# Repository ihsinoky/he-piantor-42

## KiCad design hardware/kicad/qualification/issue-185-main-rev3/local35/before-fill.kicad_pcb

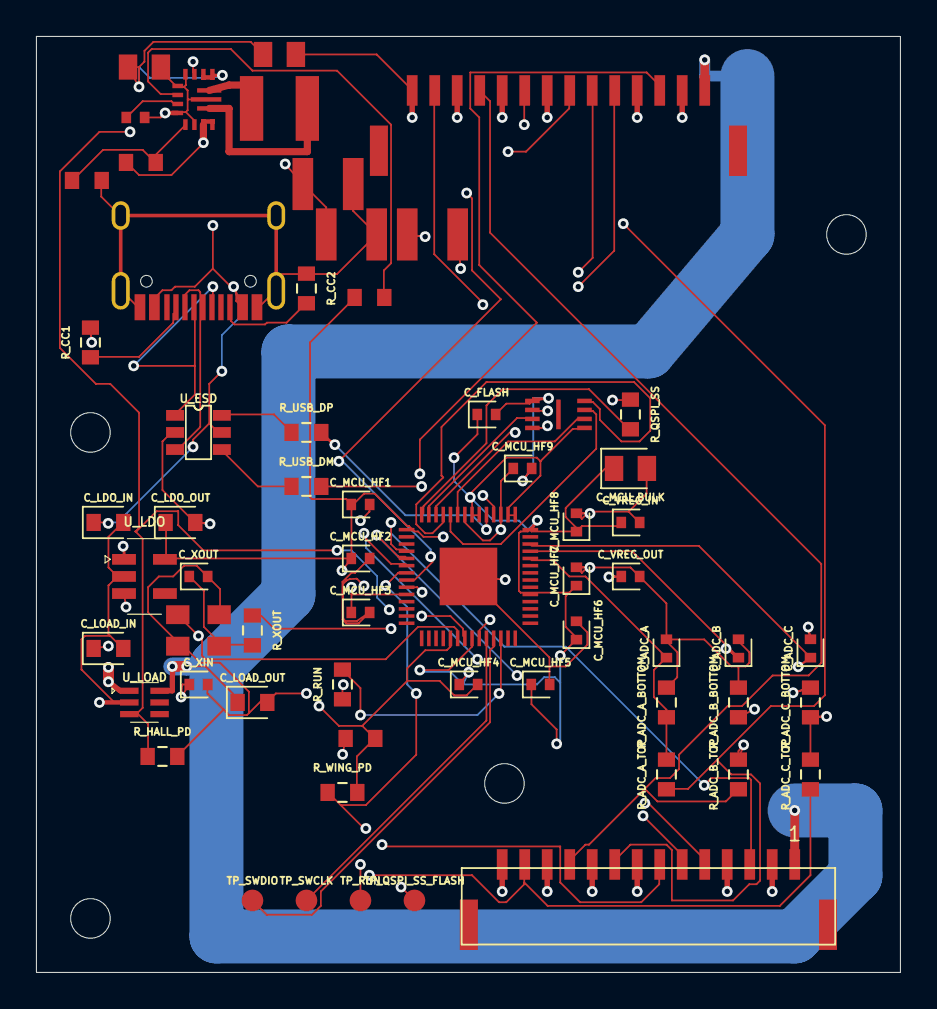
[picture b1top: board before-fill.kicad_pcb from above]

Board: 4 copper layers, 48.0 x 52.0 mm, 66 parts (0 on the bottom side), 44 nets.

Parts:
C1: 15pF; C1
C2: 15pF; C2
C3: 100nF; C3
C4: 100nF; C4
C5: 100nF; C5
C6: 100nF; C6
C7: 100nF; C7
C8: 100nF; C8
C9: 100nF; C9
C10: 100nF; C10
C11: 100nF; C11
C12: 1uF; C12
C13: 1uF; C13
C14: 10uF; C14
C15: 100nF; C15
C16: 1uF; C16
C17: 1uF; C17
C18: 1uF; C18
C19: 1uF; C19
C20: 1nF; C20
C21: 1nF; C21
C22: 1nF; C22
C23: 22uF 16V X6S 0805; C23
C24: 22uF 16V X6S 0805; C24
C25: 100nF; C25
C26: 22uF 16V X7R 1210; C26
C27: 22uF 16V X7R 1210; C27
C28: 22uF 16V X7R 1210; C28
H1: NPTH_2.2mm; H1
H2: NPTH_2.2mm; H2
H3: NPTH_2.2mm; H3
H4: NPTH_2.2mm; H4
J1: TYPE-C-31-M-12; J1
J2: BM14B-GHS-TBT(LF)(SN); J2
J3: BM14B-GHS-TBT(LF)(SN); J3
L1: 1.5uH XFL4020-152MEC; L1
R1: 5.1k; R1
R2: 5.1k; R2
R3: 27; R3
R4: 27; R4
R5: 1k; R5
R6: 100k; R6
R7: 100k; R7
R8: 10k; R8
R9: 1k; R9
R10: 6.8k; R10
R11: 10k; R11
R12: 6.8k; R12
R13: 10k; R13
R14: 6.8k; R14
R15: 10k; R15
R16: 100k; R16
R17: 54.9k 0.1% 25ppm/K; R17
R18: 10k 0.1% 25ppm/K; R18
R19: 100k; R19
TP1: TestPoint; TP1
TP2: TestPoint; TP2
TP3: TestPoint; TP3
TP4: TestPoint; TP4
U1: RP2040; U1
U2: USBLC6-2SC6; U2
U3: W25Q16JVUXIQ; U3
U4: AP2112K-3.3TRG1; U4
U5: TPS22919DCKR; U5
U6: TPS63070RNMR; U6
Y1: ABM8-272-T3; Y1

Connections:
ADC_A: C20.1, R10.2, R11.1, U1.38
ADC_B: C21.1, R12.2, R13.1, U1.39
ADC_C: C22.1, R14.2, R15.1, U1.40
CC1: J1.3, R1.1
CC2: J1.10, R2.1
FB_5V2: R17.2, R18.1, U6.5
GND: C1.2, C2.2, C3.2, C4.2, C5.2, C6.2, C7.2, C8.2, C9.2, C10.2, C11.2, C12.2, C13.2, C14.2, C15.2, C16.2, C17.2, C18.2, C19.2, C20.2, C21.2, C22.2, C23.2, C24.2, C25.2, C26.2, C27.2, C28.2, J1.1, J1.12, J1.13, J2.2, J2.4, J2.8, J2.10, J2.12, J2.14, J3.2, J3.4, J3.8, J3.10, J3.12, J3.14, R1.2, R2.2, R6.2, R7.2, R11.2, R13.2, R15.2, R16.2, R18.2, U1.19, U1.57, U2.2, U3.4, U4.2, U5.2, U6.1, U6.4, U6.6, U6.10, U6.15, Y1.2, Y1.4
HALL_5V: C19.1, J2.1, J3.1, U5.6
HALL_PWR_EN: R7.1, U1.9, U5.3, U6.14
MUX_A0: J2.3, J3.3, U1.4
MUX_A1: J2.5, J3.5, U1.5
MUX_A2: J2.6, J3.6, U1.6
MUX_EN1: J3.7, R16.1, U1.8
MUX_OUT_A: J2.9, J3.9, R10.1
MUX_OUT_B: J2.11, J3.11, R12.1
MUX_OUT_C: J2.13, J3.13, R14.1
QSPI_SCLK: U1.52, U3.6
QSPI_SD0: U1.53, U3.5
QSPI_SD1: U1.55, U3.2
QSPI_SD2: U1.54, U3.3
QSPI_SD3: U1.51, U3.7
QSPI_SS_FLASH: R5.2, TP4.1, U3.1
QSPI_SS_MCU: R5.1, U1.56
RAIL_PG: R19.2, U6.2
RUN: R8.2, TP3.1, U1.26
SW1: L1.1, U6.11
SW2: L1.2, U6.9
SWCLK: TP2.1, U1.24
SWDIO: TP1.1, U1.25
USB_DM: R4.2, U1.46
USB_DM_CONN: J1.5, J1.8, U2.3
USB_DM_ESD: R4.1, U2.4
USB_DP: R3.2, U1.47
USB_DP_CONN: J1.4, J1.9, U2.1
USB_DP_ESD: R3.1, U2.6
V1V1: C11.1, C13.1, U1.23, U1.45, U1.50
V3V3: C3.1, C4.1, C5.1, C6.1, C7.1, C8.1, C9.1, C10.1, C12.1, C14.1, C15.1, C17.1, R8.1, R19.1, U1.1, U1.10, U1.22, U1.33, U1.42, U1.43, U1.44, U1.48, U1.49, U3.8, U4.5
V5V2: C26.1, C27.1, C28.1, R17.1, U5.1, U6.7, U6.8
VAUX: C25.1, U6.3
VBUS: C16.1, C18.1, C23.1, C24.1, J1.2, J1.11, U2.5, U4.1, U4.3, U6.12, U6.13
WING_EN: J2.7, R6.1, U1.7
XIN: C1.1, U1.20, Y1.1
XOUT: R9.2, U1.21
XOUT_XTAL: C2.1, R9.1, Y1.3

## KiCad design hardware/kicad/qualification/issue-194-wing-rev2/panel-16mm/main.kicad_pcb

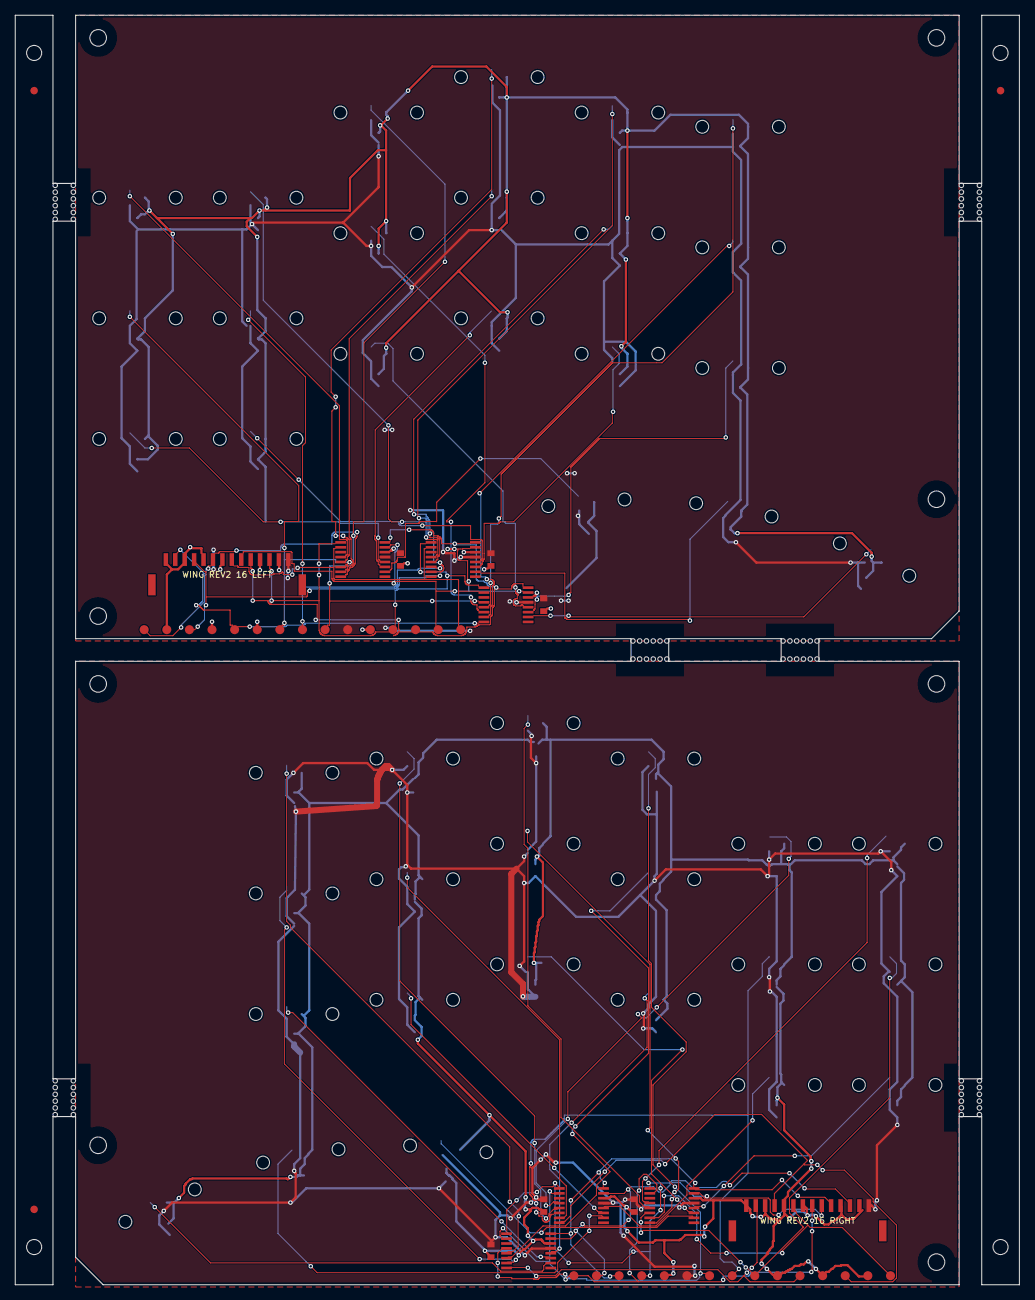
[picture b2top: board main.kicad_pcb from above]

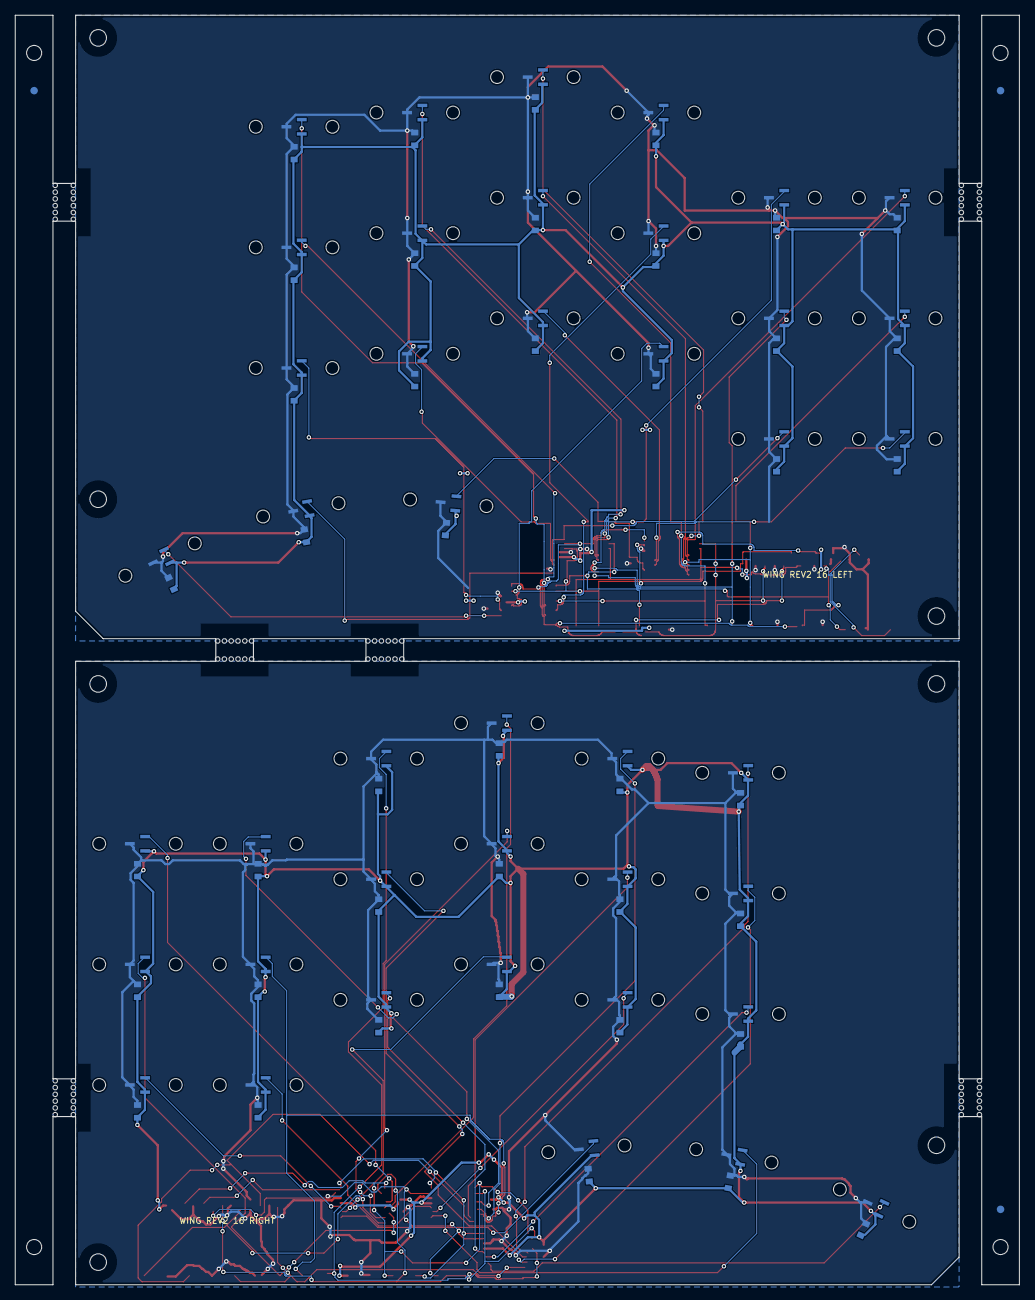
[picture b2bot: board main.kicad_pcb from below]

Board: 2 copper layers, 133.2 x 168.4 mm, 299 parts (84 on the bottom side), 60 nets.

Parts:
FID1, FID2, FID3: Fiducial_1mm
L_C_HA0, L_C_HA1, L_C_HA2, L_C_HA3, L_C_HA4, L_C_HA5, L_C_HA6: GRM188R71C104KA01D; capacitor
L_C_HB0, L_C_HB1, L_C_HB2, L_C_HB3, L_C_HB4, L_C_HB5, L_C_HB6: GRM188R71C104KA01D; capacitor
L_C_HC0, L_C_HC1, L_C_HC2, L_C_HC3, L_C_HC4, L_C_HC5, L_C_HC6: GRM188R71C104KA01D; capacitor
L_C_MUX_A: GRM188R71C104KA01D; capacitor
L_C_MUX_B: GRM188R71C104KA01D; capacitor
L_C_MUX_C: GRM188R71C104KA01D; capacitor
L_H1, L_H2, L_H3, L_H4: NPTH_2.2; NPTH
L_J_WING: BM14B-GHS-TBT(LF)(SN); connector
L_MH_1_1, L_MH_1_2, L_MH_2_1, L_MH_2_2, L_MH_3_1, L_MH_3_2, L_MH_4_1, L_MH_4_2, L_MH_5_1, L_MH_5_2, L_MH_6_1, L_MH_6_2, L_MH_7_1, L_MH_7_2, L_MH_8_1, L_MH_8_2, L_MH_9_1, L_MH_9_2, L_MH_10_1, L_MH_10_2, L_MH_11_1, L_MH_11_2, L_MH_12_1, L_MH_12_2, L_MH_13_1, L_MH_13_2, L_MH_14_1, L_MH_14_2, L_MH_15_1, L_MH_15_2, L_MH_16_1, L_MH_16_2, L_MH_17_1, L_MH_17_2, L_MH_18_1, L_MH_18_2, L_MH_19_1, L_MH_19_2, L_MH_20_1, L_MH_20_2, L_MH_21_1, L_MH_21_2: NPTH_1.7; NPTH
L_TP_H_CTR_RAW: PCB_PAD_1.2MM; testpoint
L_TP_H_DIAG_RAW: PCB_PAD_1.2MM; testpoint
L_TP_H_N_RAW: PCB_PAD_1.2MM; testpoint
L_TP_W_A0, L_TP_W_A1, L_TP_W_A2: PCB_PAD_1.2MM; testpoint
L_TP_W_EN: PCB_PAD_1.2MM; testpoint
L_TP_W_GND: PCB_PAD_1.2MM; testpoint
L_TP_W_GND_A: PCB_PAD_1.2MM; testpoint
L_TP_W_GND_B: PCB_PAD_1.2MM; testpoint
L_TP_W_GND_C: PCB_PAD_1.2MM; testpoint
L_TP_W_H5V: PCB_PAD_1.2MM; testpoint
L_TP_W_MUXA: PCB_PAD_1.2MM; testpoint
L_TP_W_MUXB: PCB_PAD_1.2MM; testpoint
L_TP_W_MUXC: PCB_PAD_1.2MM; testpoint
L_U_HA0, L_U_HA1, L_U_HA2, L_U_HA3, L_U_HA4, L_U_HA5, L_U_HA6: DRV5055A3QDBZR; hall
L_U_HB0, L_U_HB1, L_U_HB2, L_U_HB3, L_U_HB4, L_U_HB5, L_U_HB6: DRV5055A3QDBZR; hall
L_U_HC0, L_U_HC1, L_U_HC2, L_U_HC3, L_U_HC4, L_U_HC5, L_U_HC6: DRV5055A3QDBZR; hall
L_U_MUX_A: TMUX1208PWR; mux
L_U_MUX_B: TMUX1208PWR; mux
L_U_MUX_C: TMUX1208PWR; mux
MB_1, MB_2, MB_3, MB_4, MB_5, MB_6, MB_7, MB_8, MB_9, MB_10, MB_11, MB_12, MB_13, MB_14, MB_15, MB_16, MB_17, MB_18, MB_19, MB_20, MB_21, MB_22, MB_23, MB_24, MB_25, MB_26, MB_27, MB_28, MB_29, MB_30, MB_31, MB_32, MB_33, MB_34, MB_35, MB_36, MB_37, MB_38, MB_39, MB_40, MB_41, MB_42, MB_43, MB_44, MB_45, MB_46, MB_47, MB_48, MB_49, MB_50, MB_51, MB_52, MB_53, MB_54, MB_55, MB_56, MB_57, MB_58, MB_59, MB_60, MB_61, MB_62, MB_63, MB_64, MB_65, MB_66, MB_67, MB_68, MB_69, MB_70, MB_71, MB_72: NPTH_0.6
R_C_HA0, R_C_HA1, R_C_HA2, R_C_HA3, R_C_HA4, R_C_HA5, R_C_HA6: GRM188R71C104KA01D; capacitor
R_C_HB0, R_C_HB1, R_C_HB2, R_C_HB3, R_C_HB4, R_C_HB5, R_C_HB6: GRM188R71C104KA01D; capacitor
R_C_HC0, R_C_HC1, R_C_HC2, R_C_HC3, R_C_HC4, R_C_HC5, R_C_HC6: GRM188R71C104KA01D; capacitor
R_C_MUX_A: GRM188R71C104KA01D; capacitor
R_C_MUX_B: GRM188R71C104KA01D; capacitor
R_C_MUX_C: GRM188R71C104KA01D; capacitor
R_H1, R_H2, R_H3, R_H4: NPTH_2.2; NPTH
R_J_WING: BM14B-GHS-TBT(LF)(SN); connector
R_MH_1_1, R_MH_1_2, R_MH_2_1, R_MH_2_2, R_MH_3_1, R_MH_3_2, R_MH_4_1, R_MH_4_2, R_MH_5_1, R_MH_5_2, R_MH_6_1, R_MH_6_2, R_MH_7_1, R_MH_7_2, R_MH_8_1, R_MH_8_2, R_MH_9_1, R_MH_9_2, R_MH_10_1, R_MH_10_2, R_MH_11_1, R_MH_11_2, R_MH_12_1, R_MH_12_2, R_MH_13_1, R_MH_13_2, R_MH_14_1, R_MH_14_2, R_MH_15_1, R_MH_15_2, R_MH_16_1, R_MH_16_2, R_MH_17_1, R_MH_17_2, R_MH_18_1, R_MH_18_2, R_MH_19_1, R_MH_19_2, R_MH_20_1, R_MH_20_2, R_MH_21_1, R_MH_21_2: NPTH_1.7; NPTH
R_TP_H_CTR_RAW: PCB_PAD_1.2MM; testpoint
R_TP_H_DIAG_RAW: PCB_PAD_1.2MM; testpoint
R_TP_H_N_RAW: PCB_PAD_1.2MM; testpoint
R_TP_W_A0, R_TP_W_A1, R_TP_W_A2: PCB_PAD_1.2MM; testpoint
R_TP_W_EN: PCB_PAD_1.2MM; testpoint
R_TP_W_GND: PCB_PAD_1.2MM; testpoint
R_TP_W_GND_A: PCB_PAD_1.2MM; testpoint
R_TP_W_GND_B: PCB_PAD_1.2MM; testpoint
R_TP_W_GND_C: PCB_PAD_1.2MM; testpoint
R_TP_W_H5V: PCB_PAD_1.2MM; testpoint
R_TP_W_MUXA: PCB_PAD_1.2MM; testpoint
R_TP_W_MUXB: PCB_PAD_1.2MM; testpoint
R_TP_W_MUXC: PCB_PAD_1.2MM; testpoint
R_U_HA0, R_U_HA1, R_U_HA2, R_U_HA3, R_U_HA4, R_U_HA5, R_U_HA6: DRV5055A3QDBZR; hall
R_U_HB0, R_U_HB1, R_U_HB2, R_U_HB3, R_U_HB4, R_U_HB5, R_U_HB6: DRV5055A3QDBZR; hall
R_U_HC0, R_U_HC1, R_U_HC2, R_U_HC3, R_U_HC4, R_U_HC5, R_U_HC6: DRV5055A3QDBZR; hall
R_U_MUX_A: TMUX1208PWR; mux
R_U_MUX_B: TMUX1208PWR; mux
R_U_MUX_C: TMUX1208PWR; mux
TOOL_1, TOOL_2, TOOL_3, TOOL_4: NPTH_2

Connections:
L_GND: L_C_HA0.2, L_C_HA1.2, L_C_HA2.2, L_C_HA3.2, L_C_HA4.2, L_C_HA5.2, L_C_HA6.2, L_C_HB0.2, L_C_HB1.2, L_C_HB2.2, L_C_HB3.2, L_C_HB4.2, L_C_HB5.2, L_C_HB6.2, L_C_HC0.2, L_C_HC1.2, L_C_HC2.2, L_C_HC3.2, L_C_HC4.2, L_C_HC5.2, L_C_HC6.2, L_C_MUX_A.2, L_C_MUX_B.2, L_C_MUX_C.2, L_J_WING.2, L_J_WING.4, L_J_WING.8, L_J_WING.10, L_J_WING.12, L_J_WING.14, L_TP_W_GND.1, L_TP_W_GND_A.1, L_TP_W_GND_B.1, L_TP_W_GND_C.1, L_U_HA0.3, L_U_HA1.3, L_U_HA2.3, L_U_HA3.3, L_U_HA4.3, L_U_HA5.3, L_U_HA6.3, L_U_HB0.3, L_U_HB1.3, L_U_HB2.3, L_U_HB3.3, L_U_HB4.3, L_U_HB5.3, L_U_HB6.3, L_U_HC0.3, L_U_HC1.3, L_U_HC2.3, L_U_HC3.3, L_U_HC4.3, L_U_HC5.3, L_U_HC6.3, L_U_MUX_A.14, L_U_MUX_B.14, L_U_MUX_C.14
L_HALL_5V: L_C_HA0.1, L_C_HA1.1, L_C_HA2.1, L_C_HA3.1, L_C_HA4.1, L_C_HA5.1, L_C_HA6.1, L_C_HB0.1, L_C_HB1.1, L_C_HB2.1, L_C_HB3.1, L_C_HB4.1, L_C_HB5.1, L_C_HB6.1, L_C_HC0.1, L_C_HC1.1, L_C_HC2.1, L_C_HC3.1, L_C_HC4.1, L_C_HC5.1, L_C_HC6.1, L_C_MUX_A.1, L_C_MUX_B.1, L_C_MUX_C.1, L_J_WING.1, L_TP_W_H5V.1, L_U_HA0.1, L_U_HA1.1, L_U_HA2.1, L_U_HA3.1, L_U_HA4.1, L_U_HA5.1, L_U_HA6.1, L_U_HB0.1, L_U_HB1.1, L_U_HB2.1, L_U_HB3.1, L_U_HB4.1, L_U_HB5.1, L_U_HB6.1, L_U_HC0.1, L_U_HC1.1, L_U_HC2.1, L_U_HC3.1, L_U_HC4.1, L_U_HC5.1, L_U_HC6.1, L_U_MUX_A.13, L_U_MUX_B.13, L_U_MUX_C.13
L_H_A0_RAW: L_U_HA0.2, L_U_MUX_A.4
L_H_A1_RAW: L_U_HA1.2, L_U_MUX_A.5
L_H_A2_RAW: L_TP_H_CTR_RAW.1, L_U_HA2.2, L_U_MUX_A.6
L_H_A3_RAW: L_U_HA3.2, L_U_MUX_A.7
L_H_A4_RAW: L_U_HA4.2, L_U_MUX_A.12
L_H_A5_RAW: L_U_HA5.2, L_U_MUX_A.11
L_H_A6_RAW: L_U_HA6.2, L_U_MUX_A.10
L_H_B0_RAW: L_U_HB0.2, L_U_MUX_B.4
L_H_B1_RAW: L_U_HB1.2, L_U_MUX_B.5
L_H_B2_RAW: L_TP_H_N_RAW.1, L_U_HB2.2, L_U_MUX_B.6
L_H_B3_RAW: L_U_HB3.2, L_U_MUX_B.7
L_H_B4_RAW: L_U_HB4.2, L_U_MUX_B.12
L_H_B5_RAW: L_U_HB5.2, L_U_MUX_B.11
L_H_B6_RAW: L_U_HB6.2, L_U_MUX_B.10
L_H_C0_RAW: L_TP_H_DIAG_RAW.1, L_U_HC0.2, L_U_MUX_C.4
L_H_C1_RAW: L_U_HC1.2, L_U_MUX_C.5
L_H_C2_RAW: L_U_HC2.2, L_U_MUX_C.6
L_H_C3_RAW: L_U_HC3.2, L_U_MUX_C.7
L_H_C4_RAW: L_U_HC4.2, L_U_MUX_C.12
L_H_C5_RAW: L_U_HC5.2, L_U_MUX_C.11
L_H_C6_RAW: L_U_HC6.2, L_U_MUX_C.10
L_MUX_A0: L_J_WING.3, L_TP_W_A0.1, L_U_MUX_A.1, L_U_MUX_B.1, L_U_MUX_C.1
L_MUX_A1: L_J_WING.5, L_TP_W_A1.1, L_U_MUX_A.16, L_U_MUX_B.16, L_U_MUX_C.16
L_MUX_A2: L_J_WING.6, L_TP_W_A2.1, L_U_MUX_A.15, L_U_MUX_B.15, L_U_MUX_C.15
L_MUX_OUT_A: L_J_WING.9, L_TP_W_MUXA.1, L_U_MUX_A.8
L_MUX_OUT_B: L_J_WING.11, L_TP_W_MUXB.1, L_U_MUX_B.8
L_MUX_OUT_C: L_J_WING.13, L_TP_W_MUXC.1, L_U_MUX_C.8
L_WING_EN: L_J_WING.7, L_TP_W_EN.1, L_U_MUX_A.2, L_U_MUX_B.2, L_U_MUX_C.2
R_GND: R_C_HA0.2, R_C_HA1.2, R_C_HA2.2, R_C_HA3.2, R_C_HA4.2, R_C_HA5.2, R_C_HA6.2, R_C_HB0.2, R_C_HB1.2, R_C_HB2.2, R_C_HB3.2, R_C_HB4.2, R_C_HB5.2, R_C_HB6.2, R_C_HC0.2, R_C_HC1.2, R_C_HC2.2, R_C_HC3.2, R_C_HC4.2, R_C_HC5.2, R_C_HC6.2, R_C_MUX_A.2, R_C_MUX_B.2, R_C_MUX_C.2, R_J_WING.2, R_J_WING.4, R_J_WING.8, R_J_WING.10, R_J_WING.12, R_J_WING.14, R_TP_W_GND.1, R_TP_W_GND_A.1, R_TP_W_GND_B.1, R_TP_W_GND_C.1, R_U_HA0.3, R_U_HA1.3, R_U_HA2.3, R_U_HA3.3, R_U_HA4.3, R_U_HA5.3, R_U_HA6.3, R_U_HB0.3, R_U_HB1.3, R_U_HB2.3, R_U_HB3.3, R_U_HB4.3, R_U_HB5.3, R_U_HB6.3, R_U_HC0.3, R_U_HC1.3, R_U_HC2.3, R_U_HC3.3, R_U_HC4.3, R_U_HC5.3, R_U_HC6.3, R_U_MUX_A.14, R_U_MUX_B.14, R_U_MUX_C.14
R_HALL_5V: R_C_HA0.1, R_C_HA1.1, R_C_HA2.1, R_C_HA3.1, R_C_HA4.1, R_C_HA5.1, R_C_HA6.1, R_C_HB0.1, R_C_HB1.1, R_C_HB2.1, R_C_HB3.1, R_C_HB4.1, R_C_HB5.1, R_C_HB6.1, R_C_HC0.1, R_C_HC1.1, R_C_HC2.1, R_C_HC3.1, R_C_HC4.1, R_C_HC5.1, R_C_HC6.1, R_C_MUX_A.1, R_C_MUX_B.1, R_C_MUX_C.1, R_J_WING.1, R_TP_W_H5V.1, R_U_HA0.1, R_U_HA1.1, R_U_HA2.1, R_U_HA3.1, R_U_HA4.1, R_U_HA5.1, R_U_HA6.1, R_U_HB0.1, R_U_HB1.1, R_U_HB2.1, R_U_HB3.1, R_U_HB4.1, R_U_HB5.1, R_U_HB6.1, R_U_HC0.1, R_U_HC1.1, R_U_HC2.1, R_U_HC3.1, R_U_HC4.1, R_U_HC5.1, R_U_HC6.1, R_U_MUX_A.13, R_U_MUX_B.13, R_U_MUX_C.13
R_H_A0_RAW: R_U_HA0.2, R_U_MUX_A.4
R_H_A1_RAW: R_U_HA1.2, R_U_MUX_A.5
R_H_A2_RAW: R_TP_H_CTR_RAW.1, R_U_HA2.2, R_U_MUX_A.6
R_H_A3_RAW: R_U_HA3.2, R_U_MUX_A.7
R_H_A4_RAW: R_U_HA4.2, R_U_MUX_A.12
R_H_A5_RAW: R_U_HA5.2, R_U_MUX_A.11
R_H_A6_RAW: R_U_HA6.2, R_U_MUX_A.10
R_H_B0_RAW: R_U_HB0.2, R_U_MUX_B.4
R_H_B1_RAW: R_U_HB1.2, R_U_MUX_B.5
R_H_B2_RAW: R_TP_H_N_RAW.1, R_U_HB2.2, R_U_MUX_B.6
R_H_B3_RAW: R_U_HB3.2, R_U_MUX_B.7
R_H_B4_RAW: R_U_HB4.2, R_U_MUX_B.12
R_H_B5_RAW: R_U_HB5.2, R_U_MUX_B.11
R_H_B6_RAW: R_U_HB6.2, R_U_MUX_B.10
R_H_C0_RAW: R_TP_H_DIAG_RAW.1, R_U_HC0.2, R_U_MUX_C.4
R_H_C1_RAW: R_U_HC1.2, R_U_MUX_C.5
R_H_C2_RAW: R_U_HC2.2, R_U_MUX_C.6
R_H_C3_RAW: R_U_HC3.2, R_U_MUX_C.7
R_H_C4_RAW: R_U_HC4.2, R_U_MUX_C.12
R_H_C5_RAW: R_U_HC5.2, R_U_MUX_C.11
R_H_C6_RAW: R_U_HC6.2, R_U_MUX_C.10
R_MUX_A0: R_J_WING.3, R_TP_W_A0.1, R_U_MUX_A.1, R_U_MUX_B.1, R_U_MUX_C.1
R_MUX_A1: R_J_WING.5, R_TP_W_A1.1, R_U_MUX_A.16, R_U_MUX_B.16, R_U_MUX_C.16
R_MUX_A2: R_J_WING.6, R_TP_W_A2.1, R_U_MUX_A.15, R_U_MUX_B.15, R_U_MUX_C.15
R_MUX_OUT_A: R_J_WING.9, R_TP_W_MUXA.1, R_U_MUX_A.8
R_MUX_OUT_B: R_J_WING.11, R_TP_W_MUXB.1, R_U_MUX_B.8
R_MUX_OUT_C: R_J_WING.13, R_TP_W_MUXC.1, R_U_MUX_C.8
R_WING_EN: R_J_WING.7, R_TP_W_EN.1, R_U_MUX_A.2, R_U_MUX_B.2, R_U_MUX_C.2

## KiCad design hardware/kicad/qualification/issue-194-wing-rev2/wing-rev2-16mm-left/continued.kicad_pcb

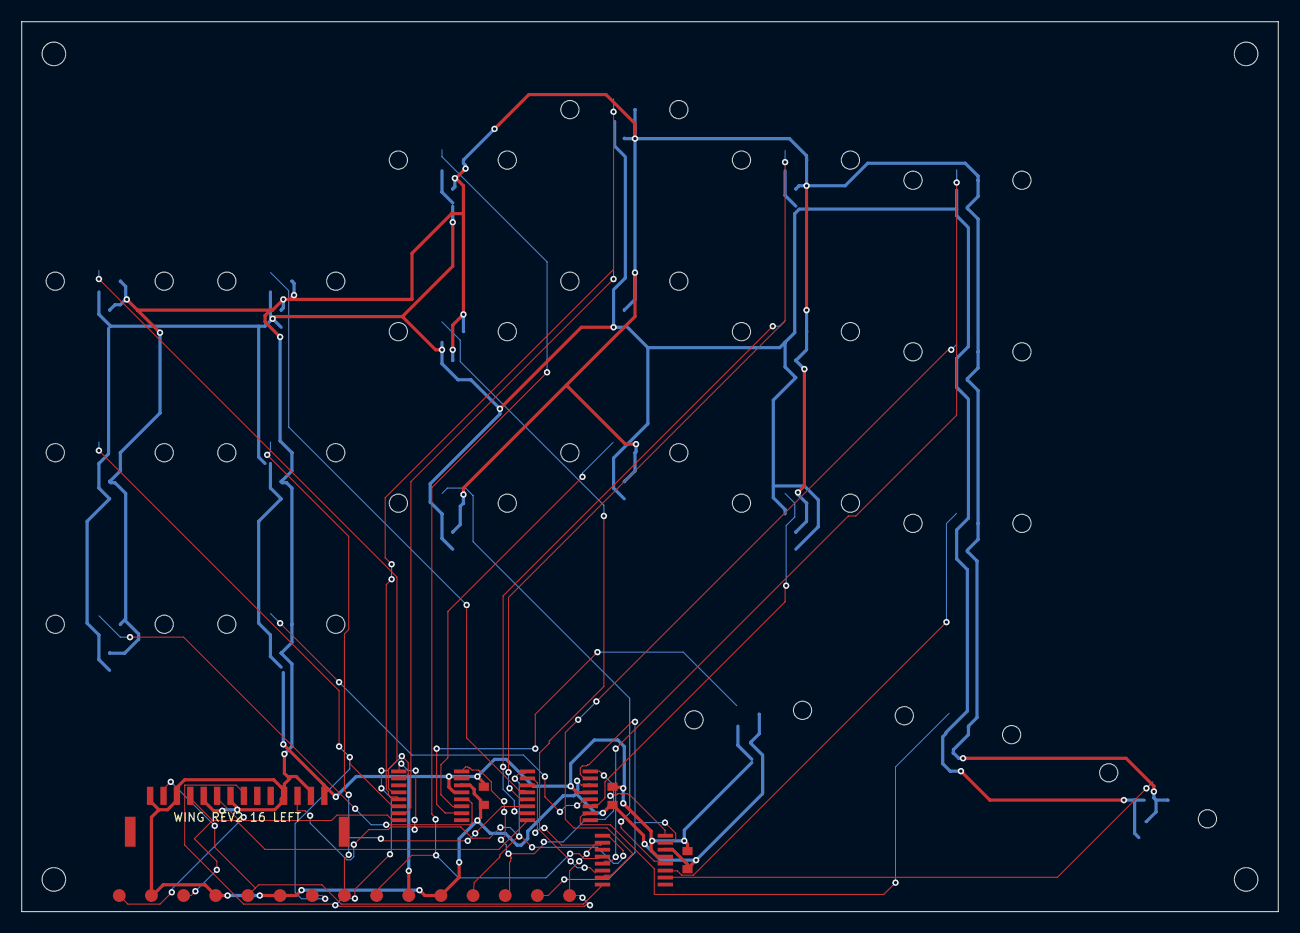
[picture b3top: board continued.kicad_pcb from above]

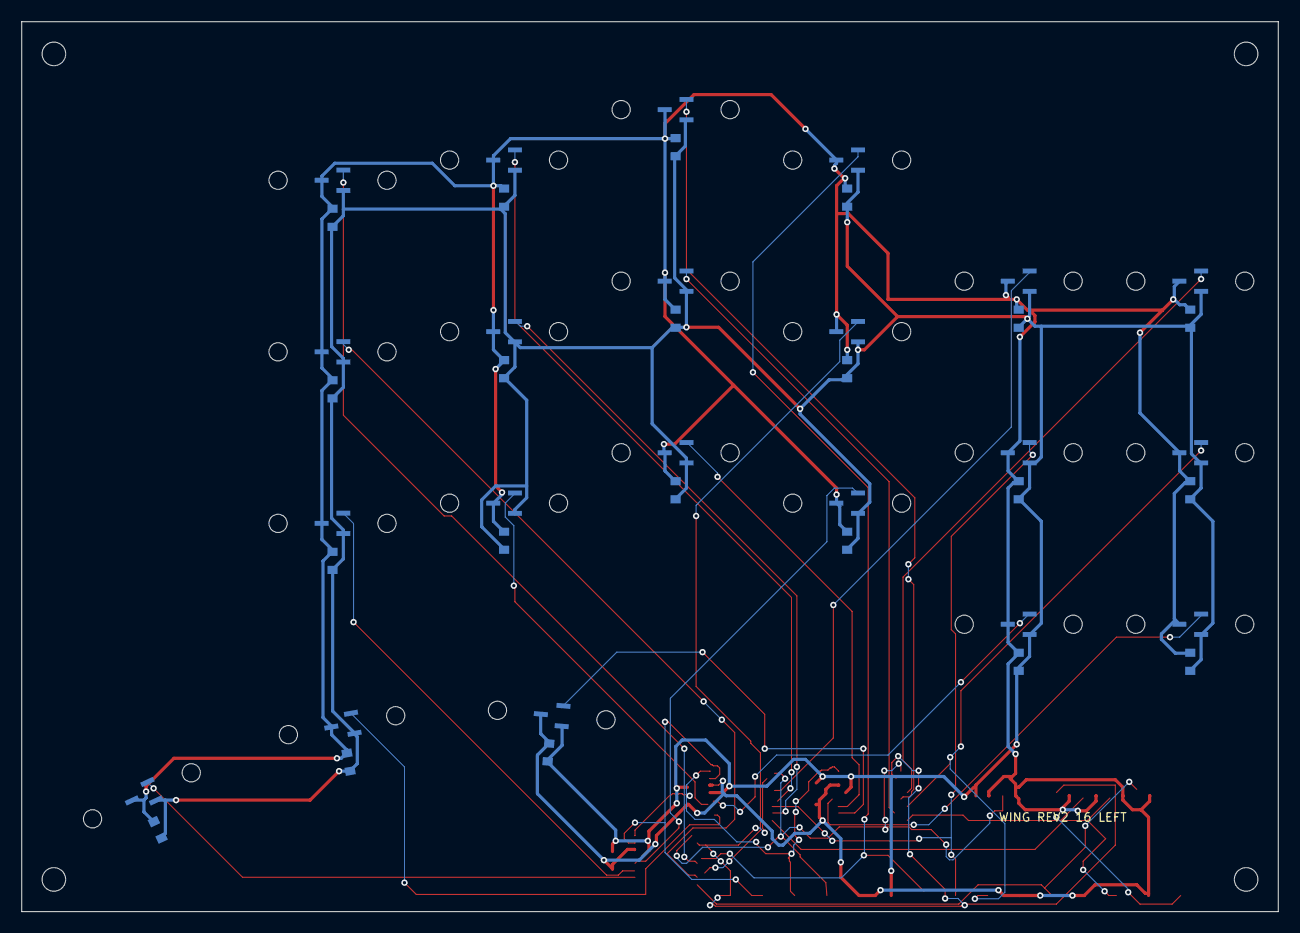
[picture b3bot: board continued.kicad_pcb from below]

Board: 2 copper layers, 117.2 x 83.0 mm, 110 parts (42 on the bottom side), 30 nets.

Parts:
C_HA0, C_HA1, C_HA2, C_HA3, C_HA4, C_HA5, C_HA6: GRM188R71C104KA01D; capacitor
C_HB0, C_HB1, C_HB2, C_HB3, C_HB4, C_HB5, C_HB6: GRM188R71C104KA01D; capacitor
C_HC0, C_HC1, C_HC2, C_HC3, C_HC4, C_HC5, C_HC6: GRM188R71C104KA01D; capacitor
C_MUX_A: GRM188R71C104KA01D; capacitor
C_MUX_B: GRM188R71C104KA01D; capacitor
C_MUX_C: GRM188R71C104KA01D; capacitor
H1, H2, H3, H4: NPTH_2.2; NPTH
J_WING: BM14B-GHS-TBT(LF)(SN); connector
MH_1_1, MH_1_2, MH_2_1, MH_2_2, MH_3_1, MH_3_2, MH_4_1, MH_4_2, MH_5_1, MH_5_2, MH_6_1, MH_6_2, MH_7_1, MH_7_2, MH_8_1, MH_8_2, MH_9_1, MH_9_2, MH_10_1, MH_10_2, MH_11_1, MH_11_2, MH_12_1, MH_12_2, MH_13_1, MH_13_2, MH_14_1, MH_14_2, MH_15_1, MH_15_2, MH_16_1, MH_16_2, MH_17_1, MH_17_2, MH_18_1, MH_18_2, MH_19_1, MH_19_2, MH_20_1, MH_20_2, MH_21_1, MH_21_2: NPTH_1.7; NPTH
TP_H_CTR_RAW: PCB_PAD_1.2MM; testpoint
TP_H_DIAG_RAW: PCB_PAD_1.2MM; testpoint
TP_H_N_RAW: PCB_PAD_1.2MM; testpoint
TP_W_A0, TP_W_A1, TP_W_A2: PCB_PAD_1.2MM; testpoint
TP_W_EN: PCB_PAD_1.2MM; testpoint
TP_W_GND: PCB_PAD_1.2MM; testpoint
TP_W_GND_A: PCB_PAD_1.2MM; testpoint
TP_W_GND_B: PCB_PAD_1.2MM; testpoint
TP_W_GND_C: PCB_PAD_1.2MM; testpoint
TP_W_H5V: PCB_PAD_1.2MM; testpoint
TP_W_MUXA: PCB_PAD_1.2MM; testpoint
TP_W_MUXB: PCB_PAD_1.2MM; testpoint
TP_W_MUXC: PCB_PAD_1.2MM; testpoint
U_HA0, U_HA1, U_HA2, U_HA3, U_HA4, U_HA5, U_HA6: DRV5055A3QDBZR; hall
U_HB0, U_HB1, U_HB2, U_HB3, U_HB4, U_HB5, U_HB6: DRV5055A3QDBZR; hall
U_HC0, U_HC1, U_HC2, U_HC3, U_HC4, U_HC5, U_HC6: DRV5055A3QDBZR; hall
U_MUX_A: TMUX1208PWR; mux
U_MUX_B: TMUX1208PWR; mux
U_MUX_C: TMUX1208PWR; mux

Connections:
GND: C_HA0.2, C_HA1.2, C_HA2.2, C_HA3.2, C_HA4.2, C_HA5.2, C_HA6.2, C_HB0.2, C_HB1.2, C_HB2.2, C_HB3.2, C_HB4.2, C_HB5.2, C_HB6.2, C_HC0.2, C_HC1.2, C_HC2.2, C_HC3.2, C_HC4.2, C_HC5.2, C_HC6.2, C_MUX_A.2, C_MUX_B.2, C_MUX_C.2, J_WING.2, J_WING.4, J_WING.8, J_WING.10, J_WING.12, J_WING.14, TP_W_GND.1, TP_W_GND_A.1, TP_W_GND_B.1, TP_W_GND_C.1, U_HA0.3, U_HA1.3, U_HA2.3, U_HA3.3, U_HA4.3, U_HA5.3, U_HA6.3, U_HB0.3, U_HB1.3, U_HB2.3, U_HB3.3, U_HB4.3, U_HB5.3, U_HB6.3, U_HC0.3, U_HC1.3, U_HC2.3, U_HC3.3, U_HC4.3, U_HC5.3, U_HC6.3, U_MUX_A.14, U_MUX_B.14, U_MUX_C.14
HALL_5V: C_HA0.1, C_HA1.1, C_HA2.1, C_HA3.1, C_HA4.1, C_HA5.1, C_HA6.1, C_HB0.1, C_HB1.1, C_HB2.1, C_HB3.1, C_HB4.1, C_HB5.1, C_HB6.1, C_HC0.1, C_HC1.1, C_HC2.1, C_HC3.1, C_HC4.1, C_HC5.1, C_HC6.1, C_MUX_A.1, C_MUX_B.1, C_MUX_C.1, J_WING.1, TP_W_H5V.1, U_HA0.1, U_HA1.1, U_HA2.1, U_HA3.1, U_HA4.1, U_HA5.1, U_HA6.1, U_HB0.1, U_HB1.1, U_HB2.1, U_HB3.1, U_HB4.1, U_HB5.1, U_HB6.1, U_HC0.1, U_HC1.1, U_HC2.1, U_HC3.1, U_HC4.1, U_HC5.1, U_HC6.1, U_MUX_A.13, U_MUX_B.13, U_MUX_C.13
H_A0_RAW: U_HA0.2, U_MUX_A.4
H_A1_RAW: U_HA1.2, U_MUX_A.5
H_A2_RAW: TP_H_CTR_RAW.1, U_HA2.2, U_MUX_A.6
H_A3_RAW: U_HA3.2, U_MUX_A.7
H_A4_RAW: U_HA4.2, U_MUX_A.12
H_A5_RAW: U_HA5.2, U_MUX_A.11
H_A6_RAW: U_HA6.2, U_MUX_A.10
H_B0_RAW: U_HB0.2, U_MUX_B.4
H_B1_RAW: U_HB1.2, U_MUX_B.5
H_B2_RAW: TP_H_N_RAW.1, U_HB2.2, U_MUX_B.6
H_B3_RAW: U_HB3.2, U_MUX_B.7
H_B4_RAW: U_HB4.2, U_MUX_B.12
H_B5_RAW: U_HB5.2, U_MUX_B.11
H_B6_RAW: U_HB6.2, U_MUX_B.10
H_C0_RAW: TP_H_DIAG_RAW.1, U_HC0.2, U_MUX_C.4
H_C1_RAW: U_HC1.2, U_MUX_C.5
H_C2_RAW: U_HC2.2, U_MUX_C.6
H_C3_RAW: U_HC3.2, U_MUX_C.7
H_C4_RAW: U_HC4.2, U_MUX_C.12
H_C5_RAW: U_HC5.2, U_MUX_C.11
H_C6_RAW: U_HC6.2, U_MUX_C.10
MUX_A0: J_WING.3, TP_W_A0.1, U_MUX_A.1, U_MUX_B.1, U_MUX_C.1
MUX_A1: J_WING.5, TP_W_A1.1, U_MUX_A.16, U_MUX_B.16, U_MUX_C.16
MUX_A2: J_WING.6, TP_W_A2.1, U_MUX_A.15, U_MUX_B.15, U_MUX_C.15
MUX_OUT_A: J_WING.9, TP_W_MUXA.1, U_MUX_A.8
MUX_OUT_B: J_WING.11, TP_W_MUXB.1, U_MUX_B.8
MUX_OUT_C: J_WING.13, TP_W_MUXC.1, U_MUX_C.8
WING_EN: J_WING.7, TP_W_EN.1, U_MUX_A.2, U_MUX_B.2, U_MUX_C.2

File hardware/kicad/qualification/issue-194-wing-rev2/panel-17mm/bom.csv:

Comment,Designator,Quantity
BM14B-GHS-TBT(LF)(SN),"L_J_WING,R_J_WING",2
DRV5055A3QDBZR,"L_U_HA0,L_U_HA1,L_U_HA2,L_U_HA3,L_U_HA4,L_U_HA5,L_U_HA6,L_U_HB0,L_U_HB1,L_U_HB2,L_U_HB3,L_U_HB4,L_U_HB5,L_U_HB6,L_U_HC0,L_U_HC1,L_U_HC2,L_U_HC3,L_U_HC4,L_U_HC5,L_U_HC6,R_U_HA0,R_U_HA1,R_U_HA2,R_U_HA3,R_U_HA4,R_U_HA5,R_U_HA6,R_U_HB0,R_U_HB1,R_U_HB2,R_U_HB3,R_U_HB4,R_U_HB5,R_U_HB6,R_U_HC0,R_U_HC1,R_U_HC2,R_U_HC3,R_U_HC4,R_U_HC5,R_U_HC6",42
GRM188R71C104KA01D,"L_C_HA0,L_C_HA1,L_C_HA2,L_C_HA3,L_C_HA4,L_C_HA5,L_C_HA6,L_C_HB0,L_C_HB1,L_C_HB2,L_C_HB3,L_C_HB4,L_C_HB5,L_C_HB6,L_C_HC0,L_C_HC1,L_C_HC2,L_C_HC3,L_C_HC4,L_C_HC5,L_C_HC6,L_C_MUX_A,L_C_MUX_B,L_C_MUX_C,R_C_HA0,R_C_HA1,R_C_HA2,R_C_HA3,R_C_HA4,R_C_HA5,R_C_HA6,R_C_HB0,R_C_HB1,R_C_HB2,R_C_HB3,R_C_HB4,R_C_HB5,R_C_HB6,R_C_HC0,R_C_HC1,R_C_HC2,R_C_HC3,R_C_HC4,R_C_HC5,R_C_HC6,R_C_MUX_A,R_C_MUX_B,R_C_MUX_C",48
TMUX1208PWR,"L_U_MUX_A,L_U_MUX_B,L_U_MUX_C,R_U_MUX_A,R_U_MUX_B,R_U_MUX_C",6
